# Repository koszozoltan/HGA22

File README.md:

HGA22 Time Signal Receiver
This project is used to receive and decode the time signals broadcasted at 135.6 kHz by the HGA22 transmitter station in Lakihegy. The system is capable of processing phase-shift keying (FSK) signals and extracting time information.

https://github.com/5an2i/USB_HGA22

📋 Features
Frequency: 135.6 kHz (LF band)

Modulation: FSK

Platform: STM32C071 Nucleo
Data format: Serial, RNDIS USB - NTP
🛠️ Hardware architecture
The following components were required for reception:

Antenna: [Ferrite rod or RFID reader antenna] tuned to 135.6 kHz.

HGA22 Time Signal Receiver
Ez a projekt a lakihegyi HGA22 adóállomás 135,6 kHz-en sugárzott pontos idő jeleinek vételére és dekódolására szolgál. A rendszer képes a fázismodulált (FSK) jelek feldolgozására és az időinformáció kinyerésére.

📋 Jellemzők
Frekvencia: 135,6 kHz (LF sáv)

Moduláció: FSK

Platform: STM32C071 Nucleo
Adatformátum: Soros , RNDIS USB - NTP 
🛠️ Hardver felépítés
A vételhez az alábbi komponensekre volt szükség:

Antenna: [Ferrit rúd vagy RFID olvasó antenna] 135,6 kHz-re hangolva.

1. Mi az a HGA22?
A HGA22 egy hosszúhullámú (LF) rádióadó Lakihegyen, amely 135,6 kHz-en sugároz. Ez az EFR (Europäische Funk-Rundsteuerung) hálózat része, amit elsősorban távvezérlésre (pl. utcai világítás, „éjszakai áram”) és pontos idő szinkronizációra használnak.

Frekvencia: 135,6 kHz

Adatsebesség: 200 bps (Baud)

Szerepe: Alternatíva a német DCF77-re, de nagyobb adatsebességgel és gyakrabban küldött időinformációval rendelkezik (akár 10 másodpercenként).

2. A Moduláció: FSK (Frequency Shift Keying)
A digitális adatokat frekvenciabillentyűzéssel kódolják. Ez azt jelenti, hogy a logikai '0' és '1' szinteket két különböző frekvencia képviseli a vivőfrekvencia körül.

Shift (löket): ±170 Hz

Frekvenciák: * F_low: 135,430 kHz (Space / 0)

F_high: 135,770 kHz (Mark / 1)
A vevő dolga, hogy eldöntse: éppen melyik frekvencia „szól”.

3. A Matematikai Motor: Goertzel-algoritmus
Hogyan detektáljunk egy konkrét frekvenciát kevés számítási kapacitással? Itt jön a Goertzel-algoritmus. Ez egy speciális IIR (Infinite Impulse Response) szűrő, amely a Diszkrét Fourier-transzformáció (DFT) egyetlen komponensét számolja ki.

Miért jobb, mint az FFT?
Mivel nekünk csak két konkrét frekvenciát (a löket alatti és feletti értékeket) kell figyelnünk, felesleges a teljes spektrumot kiszámolni. A Goertzel sokkal gyorsabb mikrokontrolleren.

A kódunkban két Goertzel szűrő fut párhuzamosan. Amelyik kimenetén nagyobb az „energia” (amplitúdó), azt a bitet tekintjük érvényesnek.

4. HGA22 Frame Parsolás (Keretezés)
Az adatok nem ömlesztve jönnek, hanem kötött szerkezetű táviratokban (frames). A protokoll (hasonlóan a Versacom-hoz) az alábbi módon épül fel:

Start karakter: 0x68 (ez jelzi a csomag elejét).

Hossz: Megadja, hány bájt következik.

Ismételt Hossz és Start: Biztonsági ellenőrzés.

Címzés: Megadja, kinek szól az üzenet (az időjel címe általában 0x00).

Adat (Payload): Itt van a lényeg! BCD kódolással tartalmazza az évet, hónapot, napot, órát, percet és másodpercet.

Checksum (CRC): Hibaellenőrzés.

Stop karakter: 0x16.

A kódban (main.cpp):
A parsoló egy állapotgépet (State Machine) használ. Addig dobálja el a bejövő bájtokat, amíg nem talál egy 0x68-at, majd elkezdi feltölteni a puffert a megadott hossz alapján.

https://cmake.org/download/

https://www.codeblocks.org/

https://developer.arm.com/downloads/-/arm-gnu-toolchain-downloads

https://sourceforge.net/projects/gnuwin32/

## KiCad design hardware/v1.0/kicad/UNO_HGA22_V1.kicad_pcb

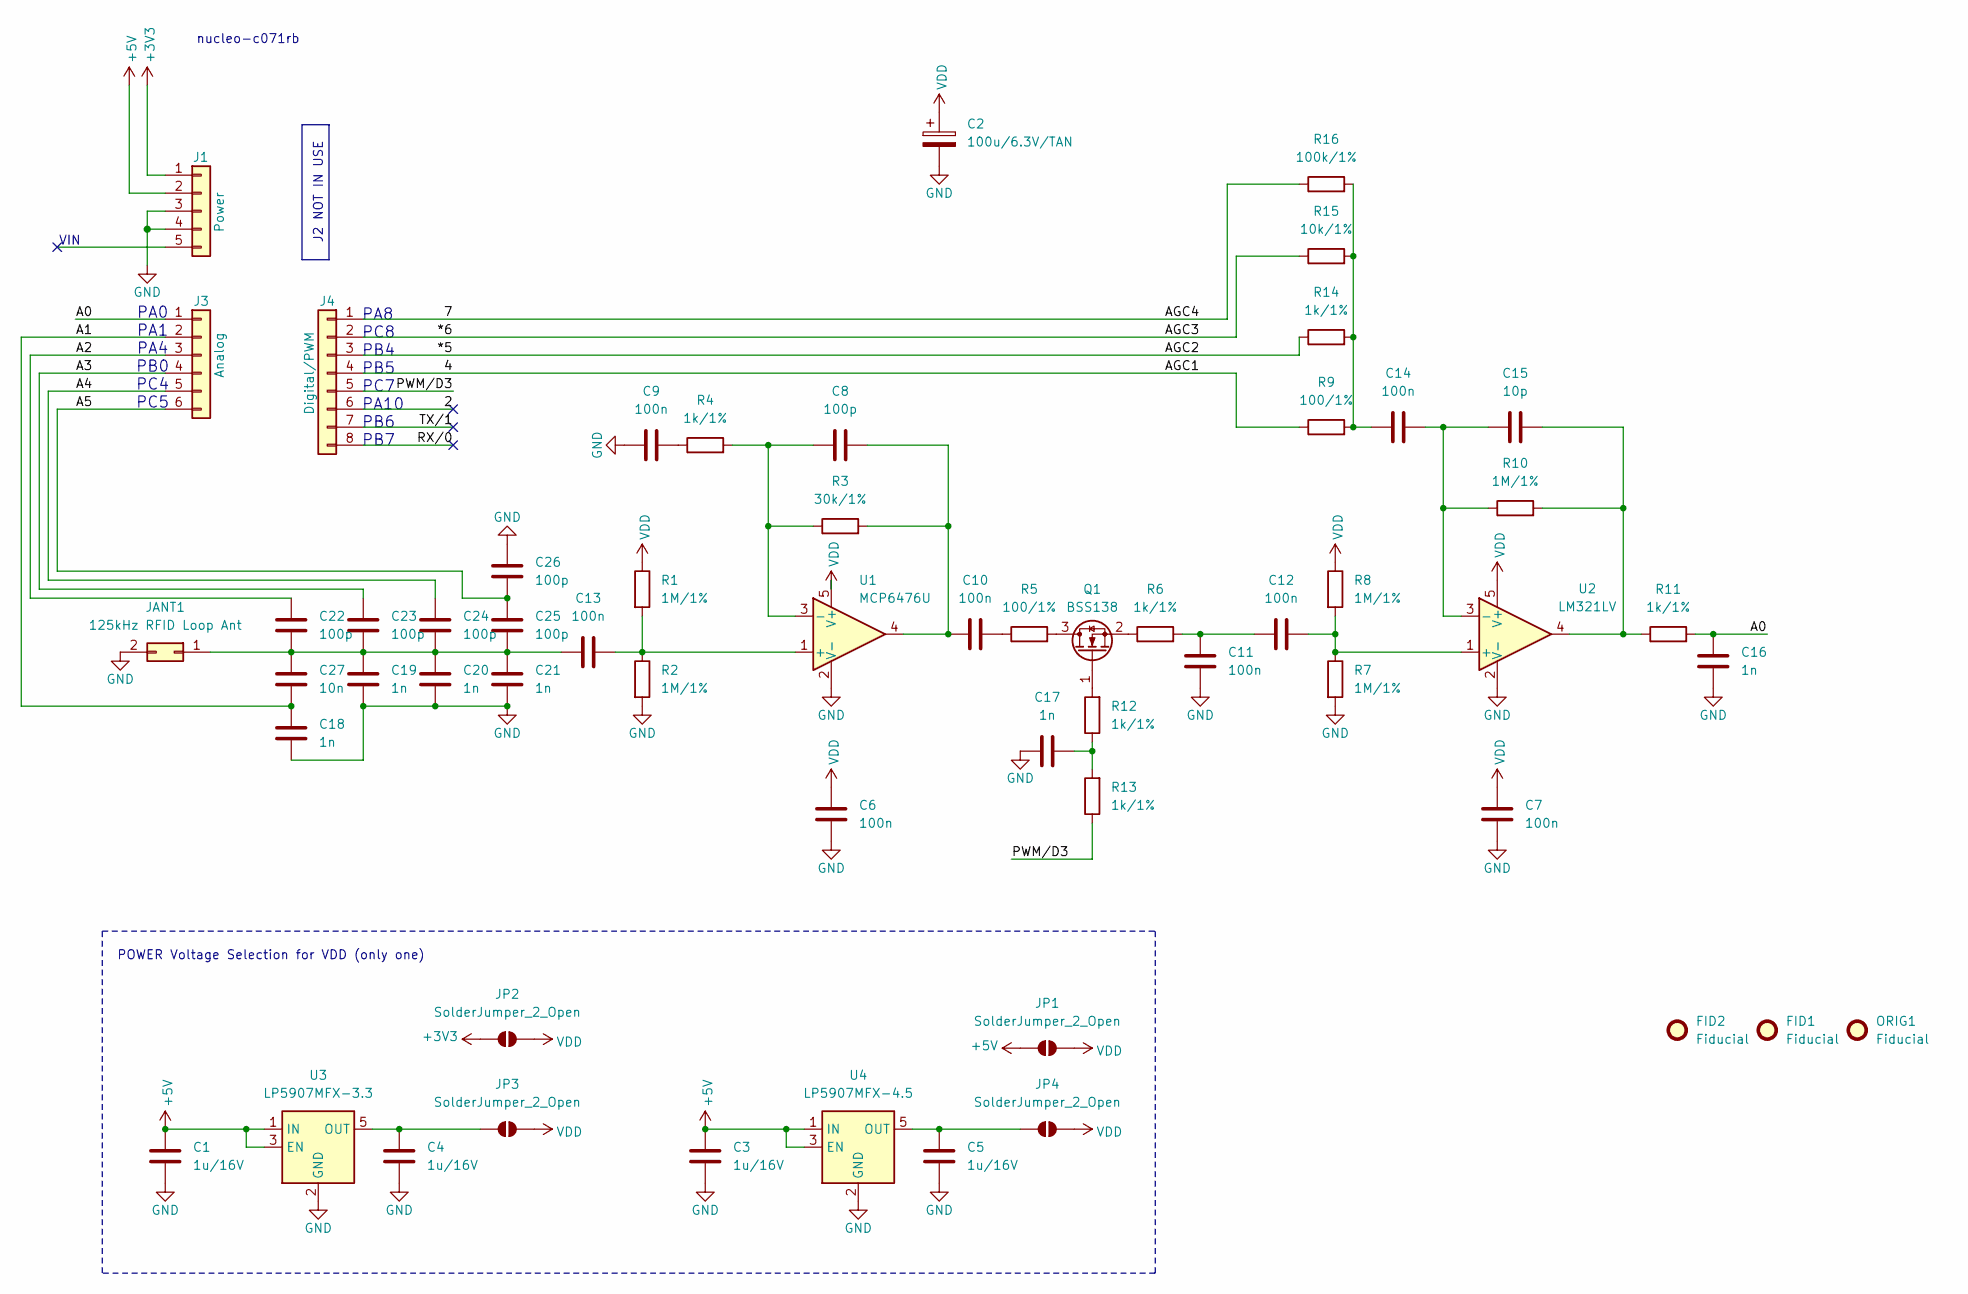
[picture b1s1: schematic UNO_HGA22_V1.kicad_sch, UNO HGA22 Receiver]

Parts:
C1, C3, C4, C5: 1u/16V; C_0805_2012Metric_Pad1.18x1.45mm_HandSolder
C2: 100u/6.3V/TAN; CP_EIA-3528-21_Kemet-B_HandSolder
C6, C7, C9, C10, C11, C12, C13, C14: 100n; C_0805_2012Metric_Pad1.18x1.45mm_HandSolder
C8, C22, C23, C24, C25, C26: 100p; C_0805_2012Metric_Pad1.18x1.45mm_HandSolder
C15: 10p; C_0805_2012Metric_Pad1.18x1.45mm_HandSolder
C16, C17, C18, C19, C20, C21: 1n; C_0805_2012Metric_Pad1.18x1.45mm_HandSolder
C27: 10n; C_0805_2012Metric_Pad1.18x1.45mm_HandSolder
FID1, FID2: Fiducial; Fiducial_1.5mm_Mask3mm
J1: Power; PinHeader_1x05_P2.54mm_Vertical
J3: Analog; PinHeader_1x06_P2.54mm_Vertical
J4: Digital/PWM; PinHeader_1x08_P2.54mm_Vertical
JANT1: 125kHz RFID Loop Ant; PinHeader_2x01_P2.54mm_Vertical
JP1, JP2, JP3, JP4: SolderJumper_2_Open; SolderJumper-2_P1.3mm_Open_TrianglePad1.0x1.5mm
ORIG1: Fiducial; Fiducial_Cross_1.5mm_Mask2mm
Q1: BSS138; SOT-23_Handsoldering
R1, R2, R7, R8, R10: 1M/1%; R_0805_2012Metric_Pad1.20x1.40mm_HandSolder
R3: 30k/1%; R_0805_2012Metric_Pad1.20x1.40mm_HandSolder
R4, R6, R11, R12, R13, R14: 1k/1%; R_0805_2012Metric_Pad1.20x1.40mm_HandSolder
R5, R9: 100/1%; R_0805_2012Metric_Pad1.20x1.40mm_HandSolder
R15: 10k/1%; R_0805_2012Metric_Pad1.20x1.40mm_HandSolder
R16: 100k/1%; R_0805_2012Metric_Pad1.20x1.40mm_HandSolder
U1: MCP6476U; SOT-23-5
U2: LM321LV; SOT-23-5
U3: LP5907MFX-3.3; SOT-23-5
U4: LP5907MFX-4.5; SOT-23-5

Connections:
+3V3: J1.1, JP2.1 (A)
+5V: C1.1, C3.1, J1.2, JP1.1 (A), U3.1 (IN), U3.3 (EN), U4.1 (IN), U4.3 (EN)
/2: J4.6
/4: J4.4, R9.1
/7: J4.1, R16.1
/*5: J4.3, R14.1
/*6: J4.2, R15.1
/A0: C16.1, J3.1, R11.2
/A1: C18.1, C27.2, J3.2
/A2: C22.2, J3.3
/A3: C23.2, J3.4
/A4: C24.2, J3.5
/A5: C25.2, C26.1, J3.6
/PWM/D3: J4.5, R13.1
/RX/0: J4.8
/TX/1: J4.7
GND: C1.2, C2.2, C3.2, C4.2, C5.2, C6.2, C7.2, C9.1, C11.2, C16.2, C17.1, C18.2, C19.2, C20.2, C21.2, C26.2, J1.3, J1.4, JANT1.2, R2.2, R7.2, U1.2 (V-), U2.2 (V-), U3.2 (GND), U4.2 (GND)
unnamed: C9.2, R4.1
unnamed: C8.2, C10.1, R3.2, U1.4
unnamed: C10.2, R5.1
unnamed: C11.1, C12.1, R6.2
unnamed: C14.1, R9.2, R14.2, R15.2, R16.2
unnamed: C15.2, R10.2, R11.1, U2.4
unnamed: C17.2, R12.1, R13.2
unnamed: C13.1, C19.1, C20.1, C21.1, C22.1, C23.1, C24.1, C25.1, C27.1, JANT1.1
unnamed: C4.1, JP3.1 (A), U3.5 (OUT)
unnamed: C5.1, JP4.1 (A), U4.5 (OUT)
unnamed: Q1.3 (D), R5.2
unnamed: Q1.1 (G), R12.2
unnamed: Q1.2 (S), R6.1
unnamed: C13.2, R1.2, R2.1, U1.1 (+)
unnamed: C8.1, R3.1, R4.2, U1.3 (-)
unnamed: C12.2, R7.1, R8.2, U2.1 (+)
unnamed: C14.2, C15.1, R10.1, U2.3 (-)
VDD: C2.1, C6.1, C7.1, JP1.2 (B), JP2.2 (B), JP3.2 (B), JP4.2 (B), R1.1, R8.1, U1.5 (V+), U2.5 (V+)

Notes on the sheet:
J2 NOT IN USE
PA0 PA1 PA4 PB0 PC4 PC5
VIN
PA8 PC8 PB4 PB5 PC7 PA10 PB6 PB7
POWER Voltage Selection for VDD (only one)
nucleo-c071rb

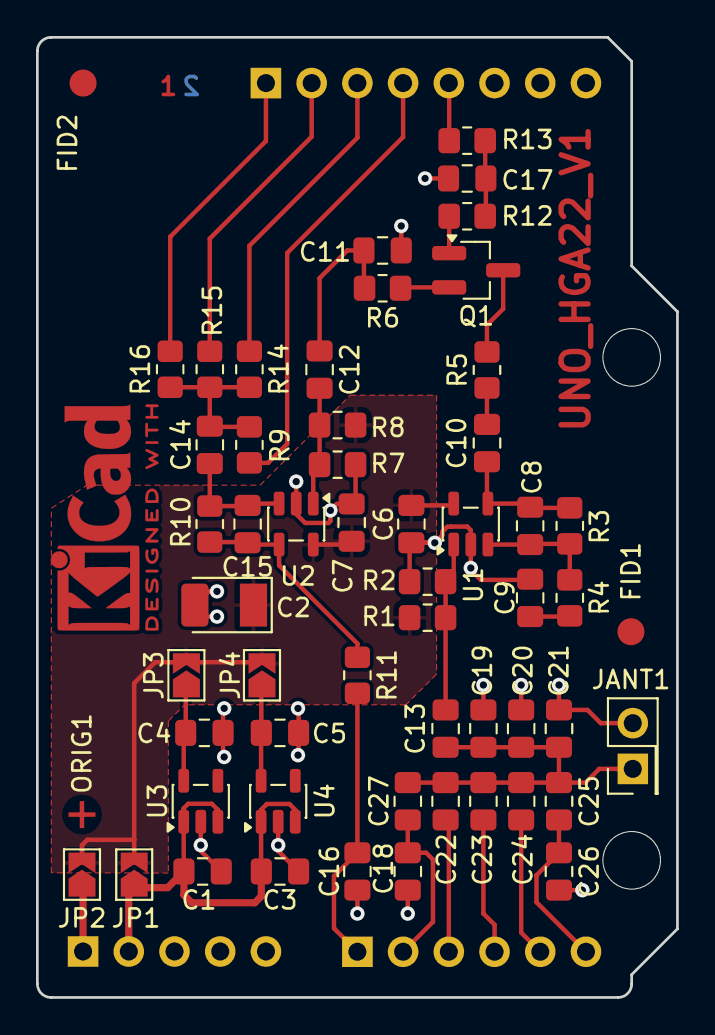
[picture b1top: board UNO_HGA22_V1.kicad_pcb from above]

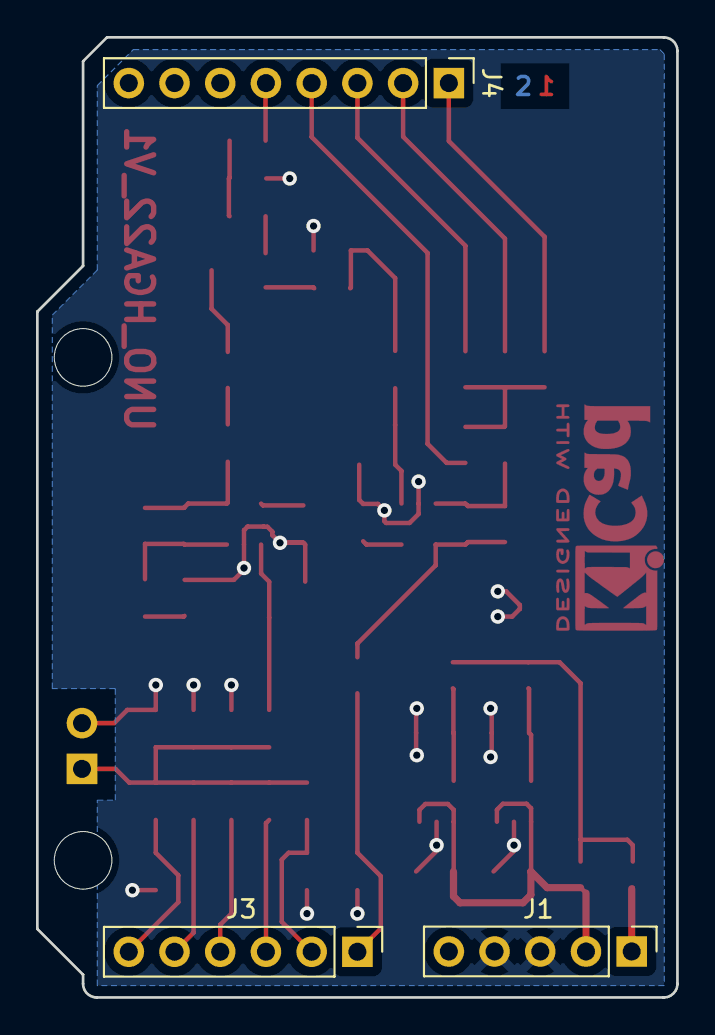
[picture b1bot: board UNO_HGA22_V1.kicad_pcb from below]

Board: 2 copper layers, 35.6 x 53.3 mm, 61 parts (3 on the bottom side), 32 nets.

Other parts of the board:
MH3, MH4: MountingHole_3.2mm

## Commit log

2026-03-06 Initial commit: HGA22 receiver
2026-03-13 Added Finished PCB and Gerber.
2026-03-17 [FIX] Goertzel mag , adc oversample ,
2026-03-18 Add files via upload
    [ADD] raw files
2026-03-18 [ADD] hga agc audacity pictures
2026-03-19 test raw without hw
2026-03-20 add pictures
2026-03-20 [ADD] agc hw process
2026-03-23 Update HW Documentation. Fixing Schematic and PCB Silkscreen. Added generated Interactive BOM.
2026-03-27 [ADD] iq demodulation
2026-03-27 [FIX] README.md
